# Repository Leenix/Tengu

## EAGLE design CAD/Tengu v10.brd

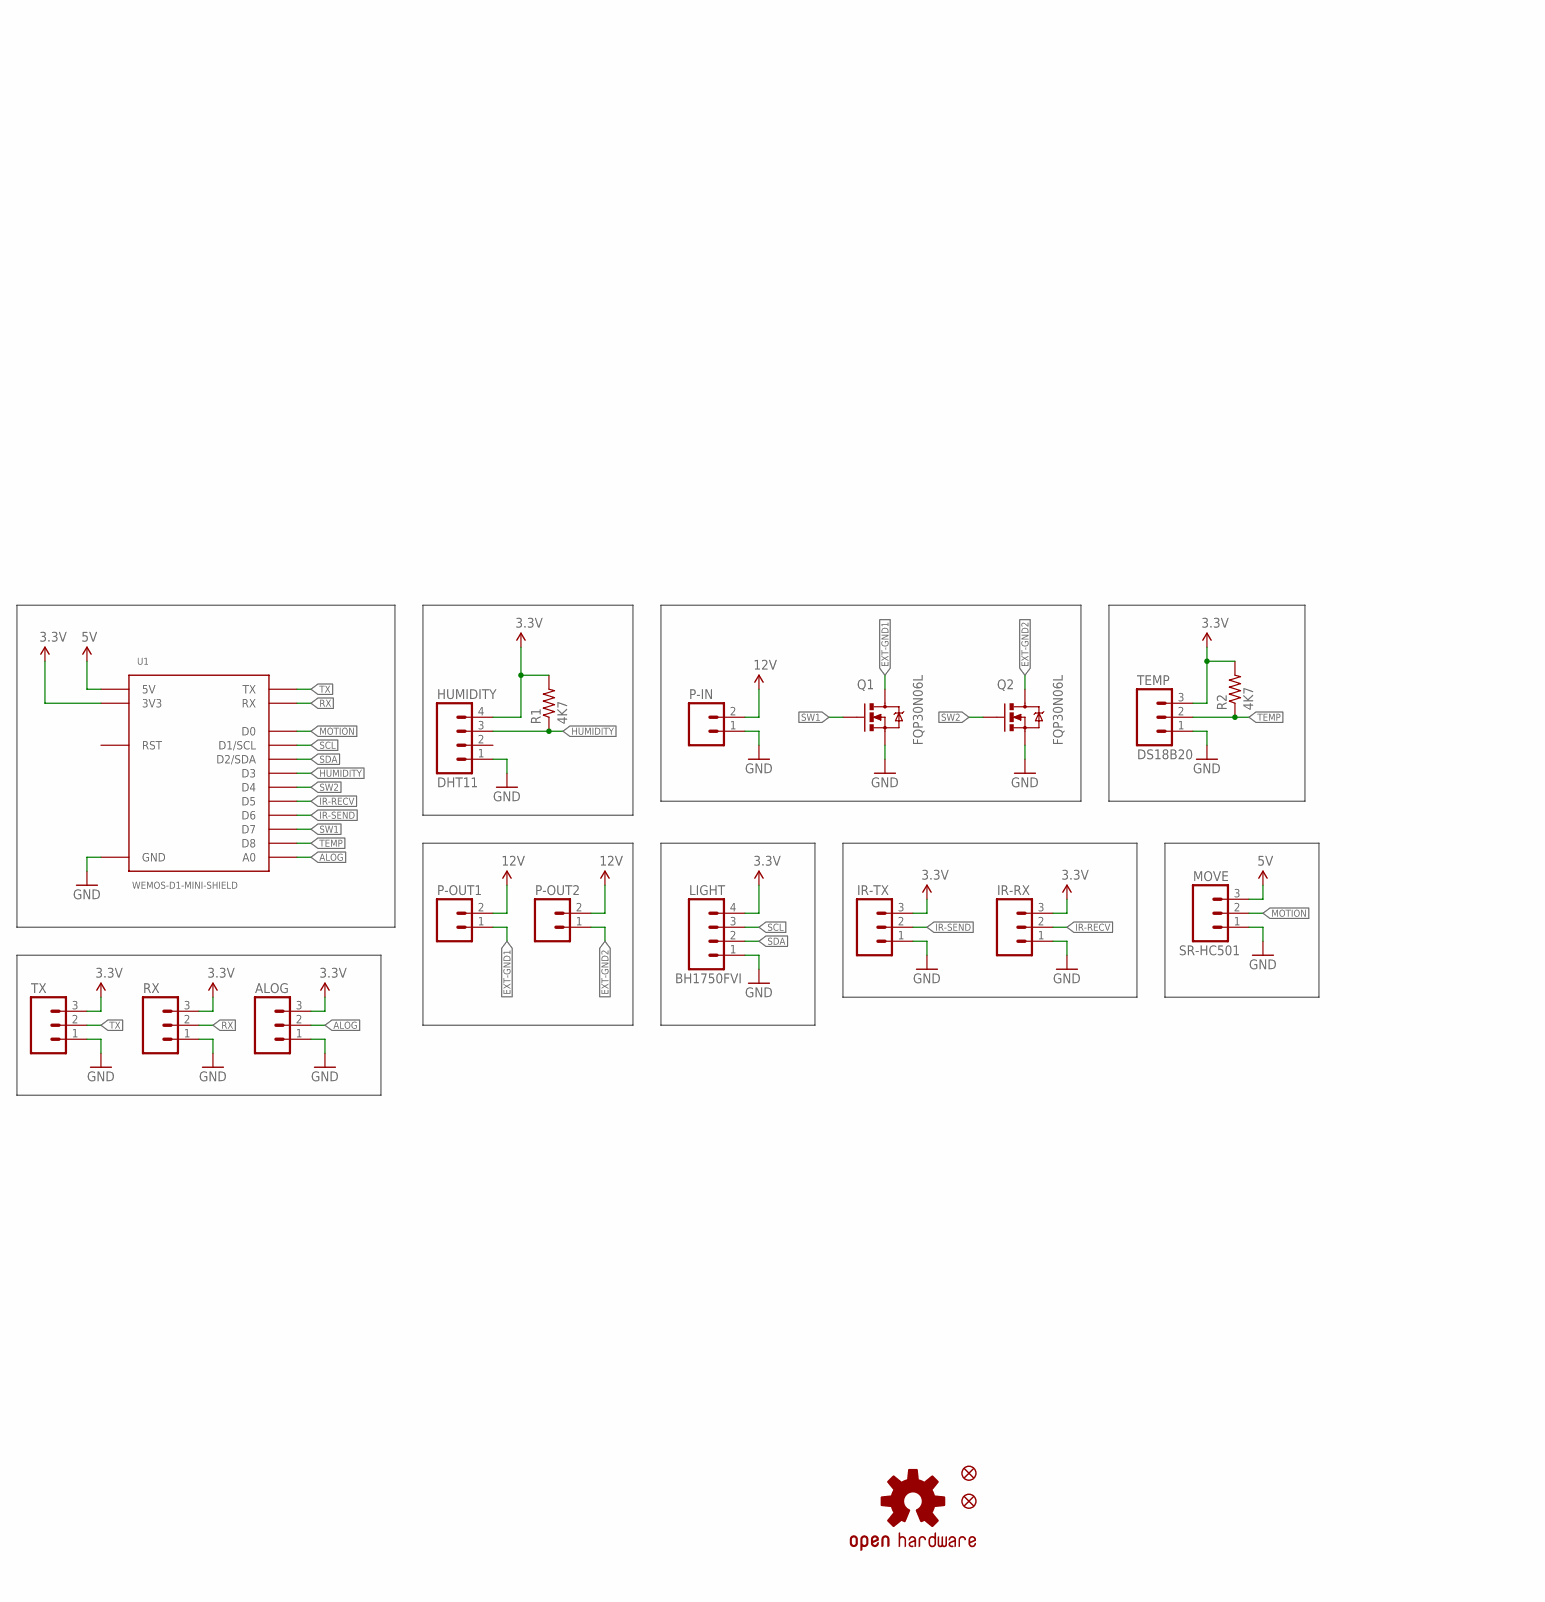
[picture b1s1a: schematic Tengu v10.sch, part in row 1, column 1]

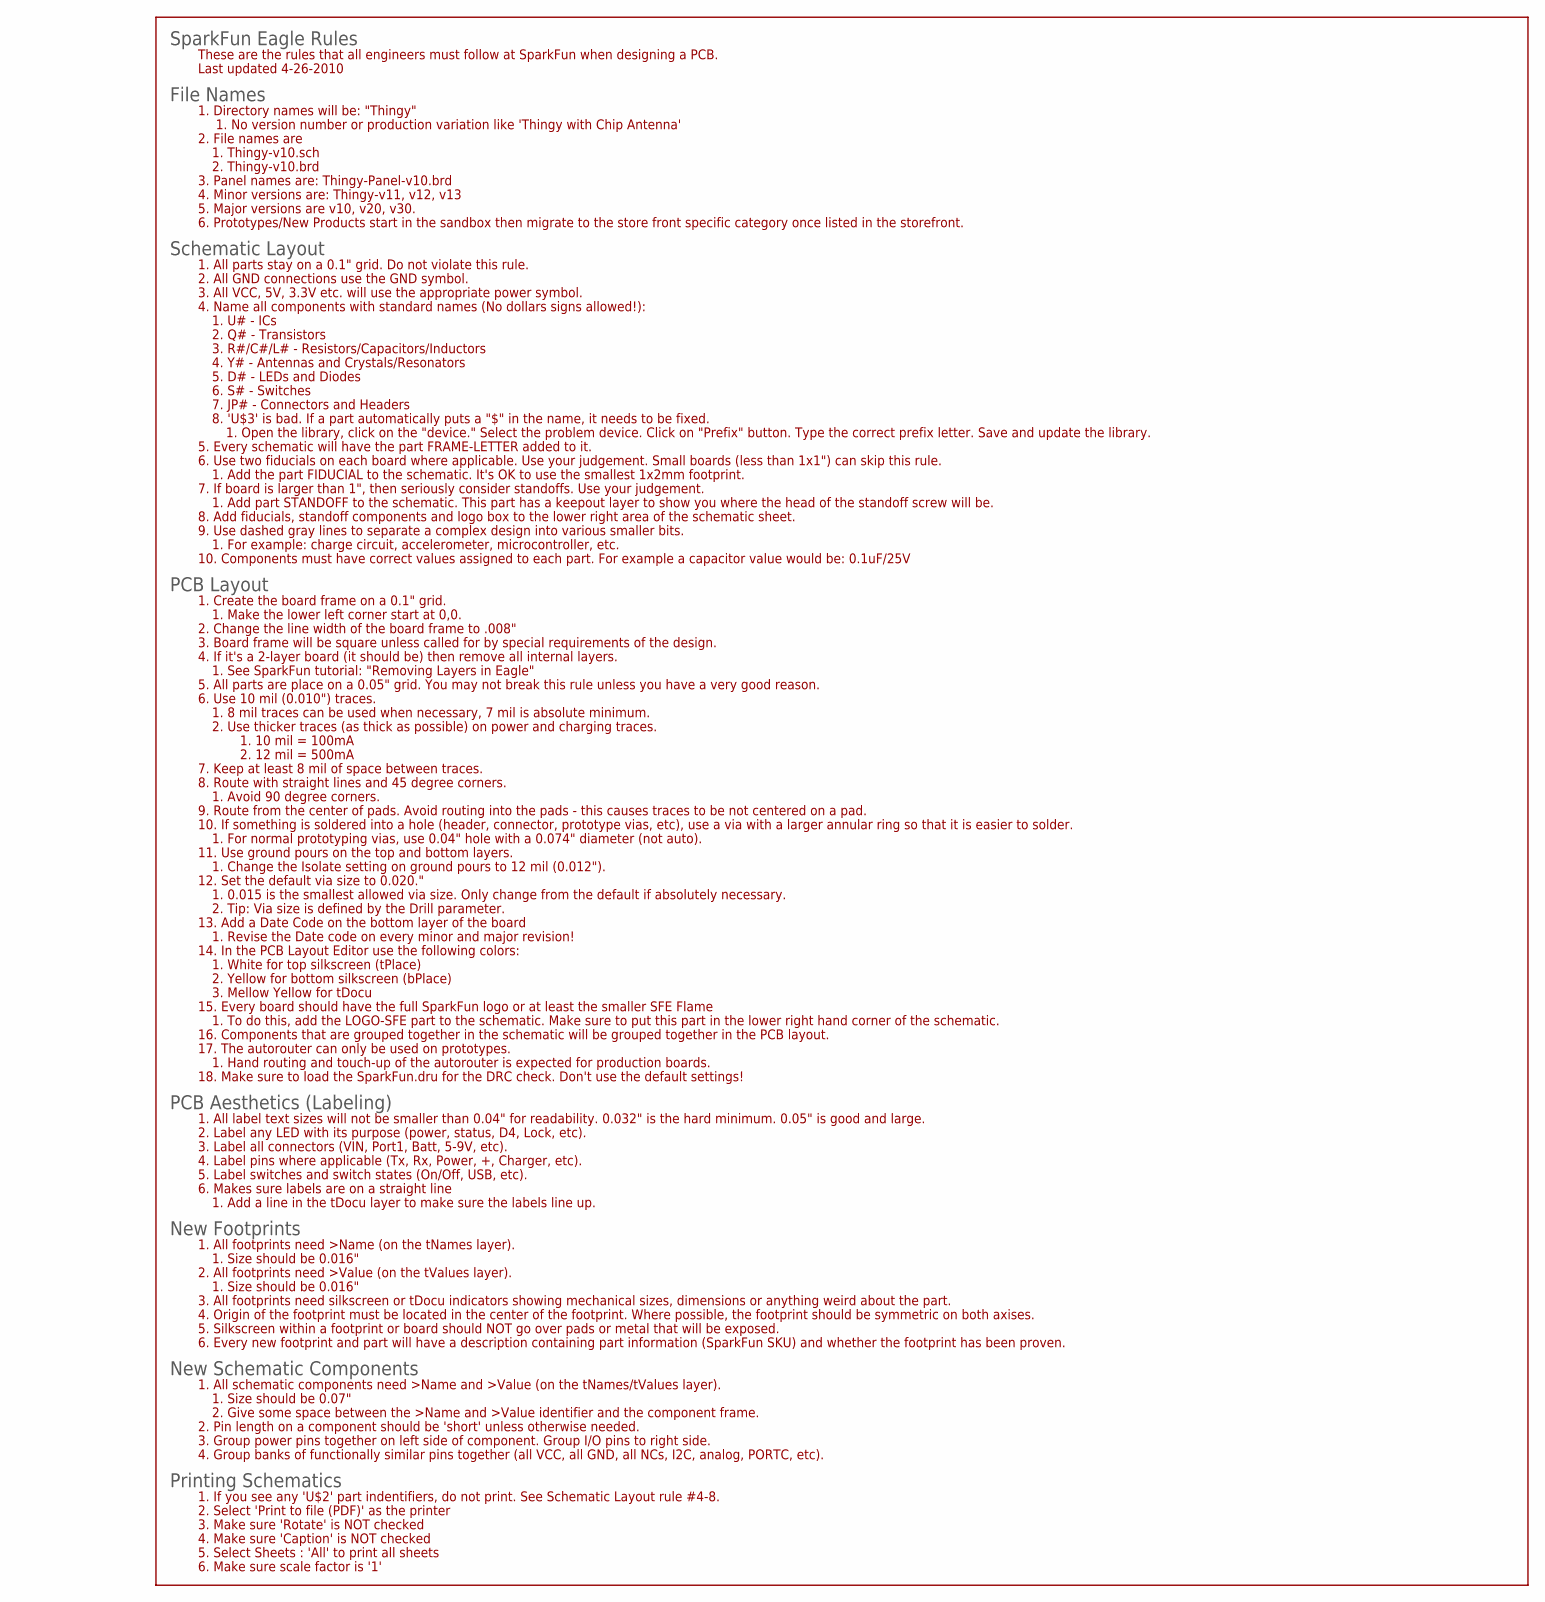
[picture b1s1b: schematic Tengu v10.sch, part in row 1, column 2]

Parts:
ALOG: M03PTH; 1X03
FD1, FD2: FIDUCIAL1X2; FIDUCIAL-1X2
HUMIDITY: DHT11; 1X04
IR-RX: M03PTH; 1X03
IR-TX: M03PTH; 1X03
LIGHT: BH1750FVI; 1X04
LOGO1: OSHW-LOGOM; OSHW-LOGO-M
MOVE: SR-HC501; 1X03
P-IN: M02PTH3; 1X02_LONGPADS
P-OUT1, P-OUT2: M02PTH3; 1X02_LONGPADS
Q1, Q2: FQP30N06L; TO220V
R1, R2: 4K7; 1206
RX: M03PTH; 1X03
TEMP: DS18B20; 1X03
TX: M03PTH; 1X03
U1: WEMOS-D1-MINI-SHIELD

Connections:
3.3V: ALOG.3, HUMIDITY.4, IR-RX.3, IR-TX.3, LIGHT.4, R1.2, R2.2, RX.3, TEMP.3, TX.3, U1.3V3
5V: MOVE.3, U1.5V
12V: P-IN.2, P-OUT1.2, P-OUT2.2
ALOG: ALOG.2, U1.A0
EXT-GND1: P-OUT1.1, Q1.2 (D)
EXT-GND2: P-OUT2.1, Q2.2 (D)
GND: ALOG.1, HUMIDITY.1, IR-RX.1, IR-TX.1, LIGHT.1, MOVE.1, P-IN.1, Q1.3 (S), Q2.3 (S), RX.1, TEMP.1, TX.1, U1.GND
HUMIDITY: HUMIDITY.3, R1.1, U1.D3
IR-RECV: IR-RX.2, U1.D5
IR-SEND: IR-TX.2, U1.D6
MOTION: MOVE.2, U1.D0
RX: RX.2, U1.RX
SCL: LIGHT.3, U1.D1 (D1/SCL)
SDA: LIGHT.2, U1.D2 (D2/SDA)
SW1: Q1.1 (G), U1.D7
SW2: Q2.1 (G), U1.D4
TEMP: R2.1, TEMP.2, U1.D8
TX: TX.2, U1.TX

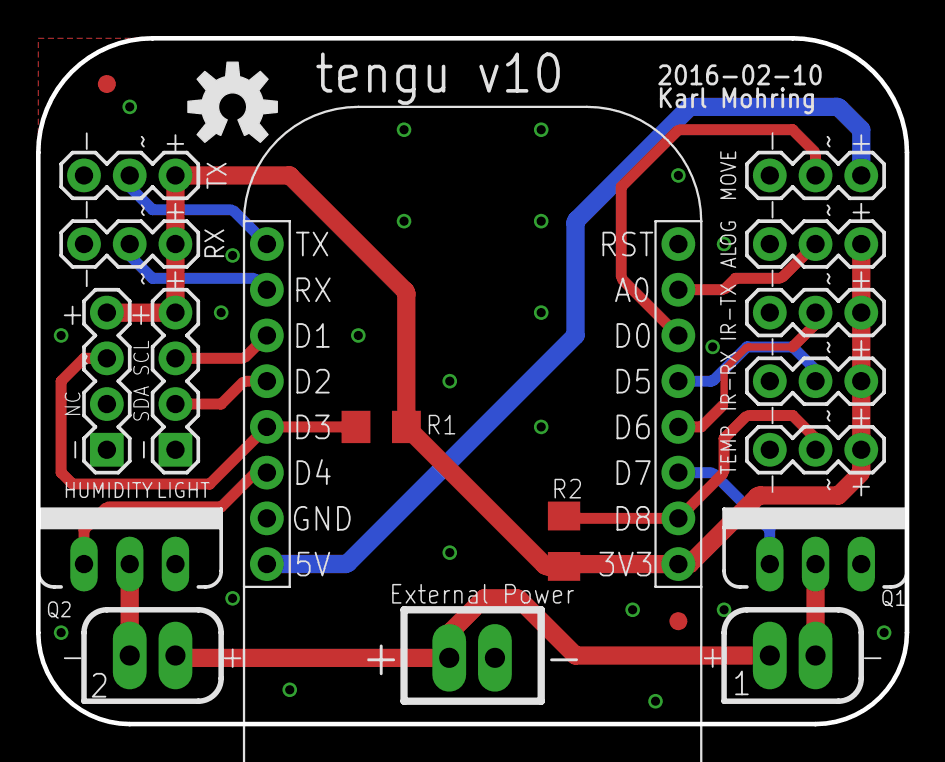
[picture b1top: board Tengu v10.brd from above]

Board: 2 copper layers, 48.3 x 38.1 mm, 20 parts (0 on the bottom side), 18 nets.

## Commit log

2016-02-19 Initial commit
    Arduino ESP8266 code almost complete
    - Need to add IR commands and maybe some web stuff
    PCB for D1 mini added
2016-02-19 Transferred JSON object to a struct
    Much better apparently; less memory leaks
2016-02-21 Added fixed BH1750FVI library - Added function headers to fix linter autocomplete
2016-04-20 Enabled Travis-CI
2016-04-20 Updated build library list
2016-04-20 Fixed missing DHT library
2019-03-03 Old files

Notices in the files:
parts and their libraries:
SparkFun-Connectors: Licensing: Creative Commons ShareAlike 4.0 International - https://creativecommons.org/licenses/by-sa/4.0
